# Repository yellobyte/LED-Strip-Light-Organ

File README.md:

# 3-Channel LED-Strip Light Organ with Arduino Nano #

A light (or color) organ is an electronic device which converts an audio signal into rhythmic light effects. Invented in the 70's they are still popular in discotheques and party rooms though.
Now that **LED Strips** became fairly cheap they can replace normal light bulbs used in the earlier years and make the color organ look more modern.

The electronic circuit of a normal light organ separates the audio signal into several frequency bands and dimms the light bulbs or LEDs according to the average level of each band.

For a decent visual impression at least 3 bands (channels) are needed: low frequencies (bass), middle frequencies and high frequencies (treble). For best visual results each channel should control a light source of different color, e.g bass = red, middle = yellow and treble = green.

## Technical Infos ##

We have 3 channels and therefore control 3 LED Strips. Their specified working voltage must be 12V DC. The maximum length of the LED Strips the device can handle is mainly determined by the current consumption (amperes per meter length) of each LED Strip and the maximum current rating of the external 12V power supply used.

To give you a real world example: The external power supply I tested the device with was a MeanWell GS90A12 with a maximum current rating of 6.7A DC. Therefore I set the overcurrent limit to 2.2A per channel (the device itself doesn't need much). That limit allowed me to use LED Strips of 5m length with 60 LEDs (Type 3528 SMD in red, yellow or green) per meter. The overcurrent protection circuitry never got triggered.

The light organ has 3 working modes: [Normal](https://github.com/yellobyte/LED-Strip-Light-Organ/blob/main/Doc/NormalMode.mp4), [Rhythm](https://github.com/yellobyte/LED-Strip-Light-Organ/blob/main/Doc/RhythmMode.mp4) and [Cyclic](https://github.com/yellobyte/LED-Strip-Light-Organ/blob/main/Doc/Cyclic.mp4), which can be selected by pressing the **mode selection** button. 

An Arduino Nano 328P continuously samples all 3 filter outputs und transforms their voltage levels into digital PWM signals which feed the output stages with their IRF540N Power MOSFETs. Overtemperature & overcurrent protection (overload OL protection) has been integrated. 

The electrical circuit had to be devided into 2 separate [PCBs](https://github.com/yellobyte/LED-Strip-Light-Organ/blob/main/Doc/BoardTop.JPG), a **Filter-PCB** and a **Power-PCB** as I only call the basic version of the Eagle Design Tool my own and PCB size is limited to Eurocard size. But this proved to be very fortunate in the end for I redesigned the output stages a few times but didn't have to redo the analog stages. Please have a look at folder [**EagleFiles**](https://github.com/yellobyte/LED-Strip-Light-Organ/blob/main/EagleFiles) for schematic & PCB details.

The block diagram of the light organ is as follows:

### The Filter-PCB: ###

The MC33078 Op amps in the pre-amplifier and AGC stages proved perfect for the task. They might be substituted with cheaper Op amps, e.g. TL082, TLC277 or MC1458 but this comes with a loss of signal quality (distortion!). Especially the MC1458 wasn't able to pull the signal fully down to the lower rail and the TLC277 showed some crossover distortion.

The cheap LM358 Op amps used in the 3 filter stages generate crossover distortion as well but this is of no consequence in that particular application.

The AGC stage is simple but very effective and produces hardly any distortion even with high input signals applied. This stage is needed in order to normalize the signal level fed into the filter stages as the signal level from the many audio sources can vary by an order of magnitude (MP3/CD/Vinyl player, FM or internet radio, etc.).

Each of the 3 filter circuits uses an Op amp and some passive components (Rs/Cs). The resistors with strange values (6k16, 14k7, 16k9, 23k7, 71k5) belong to the E48 (2%) or E96 (1%) series. The filter circuits (2nd order) were calculated with the help of **FilterLab** from Microchip. It's available at no cost, easy to use and very intuitive. 

LED1 to LED6 have been added mainly for testing purposes. They come handy when you don't have any LED-Strips available but still want to do some tests on the device. They too are PWM controlled and show the exact same visual effects as the LED-Strips would.

### The Power-PCB: ###

The Arduino Nano 328P module is an ideal device for sampling the three filter outputs and generating PWM signals needed by the power stages. It only runs on 16MHz but this proved fast enough for the task.

The code running on the Arduino Nano is available in folder [Software](https://github.com/yellobyte/LED-Strip-Light-Organ/blob/main/Software). It was generated with VSCode/PlatformIO.

The Power MOSFETs IRF540N work as High-Side Switches (in "common drain" configuration) and need a gate voltage higher than the Nano can provide in this application, thats why 12V DC-DC converters (I/O isolated -> output side floating) had to be used. The reason is that the source voltage of the MOSFETs approaches the +12V supply voltage when switched on. To keep the MOSFETs turned on the IR2125 outputs must drive the MOSFETs gate voltage 10-12V higher than the supply voltage.

Shunt resistors (R6/R12/R18 - 0.15Ohm/2W/5%/Wire) sit between the MOSFETs and the output sockets in order to measure the output current and utilize the current sense input of the MOSFET drivers IR2125. When the IR2125 detects overcurrent it shuts down immediately until the next PWM impuls. The software in the Arduino Nano detects this condition and shuts down the affected channel even longer (5 sec) before releasing it again. No harm is done at all in case you have a permanent short on the output lines, provided you properly calibrated the trigger point of course!

The power stages by design could deliver 3-4 amperes per channel without problems. In practice the limiting factor probably will be the external 12V DC power supply. The driver MOSFETs IRF540N (Idmax > 20A) operate way from their absolute maximum ratings and only get handwarm in the enclosure (Model EXN-23361-SV from Bud Industries).

A temperature sensor LM35DZ connected to an Arduino Nano analog input pin is used to measure the temperature inside the enclosure. Temperatures over 50° celsius will shut down all channels and only temperatures below 40° celsius will release them. However, during my hour long tests the temperature overload never got triggered for the temperature inside the enclosure always hovered around 35-38° celsius.

JP1/JP2/JP3 are only needed for testing purposes, in normal working mode pins 1 & 2 should be shorted in order to allow the overload signal from the IR2125 ICs reach the Arduino Nano. R2/SV3 are only used for testing purposes as well.

Push button S1 is used for selecting the working mode.

The three TVS Diodes P6KE20A (D5/D9/D13) in parallel with the output sockets have a very fast response time and protect the device from possibly harmful voltage transients that might travel in from connected LED Strips. The latter act like big antennas when a few meters long!

D1 provides a very stable reference voltage needed by the A/D converters in the Arduino Nano.

### The two [boards](https://github.com/yellobyte/LED-Strip-Light-Organ/blob/main/Doc/BoardTop.JPG) are connected as follows: ###

```c
 Filter-PCB ---  Power-PCB
      LSP7  ---  LSP9  (analog audio)
      LSP8  ---  LSP2  (+12V=)
      A-IN  ---  A-OUT (PWM channel A)
      B-IN  ---  B-OUT (PWM channel B)
      C-IN  ---  C-OUT (PWM channel C)
      A-OUT ---  A-IN  (filter output channel A)
      B-OUT ---  B-IN  (filter output channel B)
      C-OUT ---  C-IN  (filter output channel C)  
      GNDs  ---  GNDs   
```        

## How to calibrate the circuit ##

### Filter-PCB: ###
The pre-amplifier stage, the automatic gain control (AGC) stage and all three filter circuits have to be calibrated in order to produce optimal results. The procedure itself is fairly easy. Only obstacle is you need a function generator and ideally an oscilloscope. A cheap multimeter will do if you can´t get hold of such equipment but might spoil optimal performance of the device.

Necessary steps in correct order:

1) Adjust the trimpot R8 so that pins 1 & 2 of R8 are shorted (AGC is inactive that way). Apply a signal of 1kHz/0.5Vpp to X5 **or** X6 on the power board (one of the two Cinch/RCA sockets). It gets forwarded to LSP7 on the filter board (inverting input of pre-amplifier Op amp IC1A). 

2) Choose a value of R12 so that the signal level at LSP2 (output of Op amp IC1B) is close to 2.70Vpp. In my case I ended up with a R12 of 470k.

3) Increase the amplitude of the input signal to 2.0Vpp. Now adjust the trimpot R8 so that the signal level at LSP2 is close to 3.2Vpp.

At this point the pre-amplifier & AGC stages are properly calibrated. The filter stages follow:

4) Change the input signal to 50Hz/0.7Vpp and adjust R17 so that you get 3.6Vpp at LSP4.

5) Change the input signal to 1.3kHz/0.7Vpp and adjust R22 so that you get 3.6Vpp at LSP5.

6) Change the input signal to 6kHz/0.7Vpp and adjust R30 so that you get 3.6Vpp at LSP6.

That's it. The analog circuit on the **Filter-PCB** is now fully calibrated.

### Power-PCB: ###
Only the current limits of each channel (A/B/C) need to be calibrated. That's a bit tricky as you need a current running through the MOSFETs that has exactly the value you want the IR2125 to trigger. I used a cheap electronic load from Aliexpress (XY-FZ35) to accomplish that. 

Before you start make sure the Arduino Nano is REMOVED from the Power-PCB, your external power supply is NOT attached to the 12V power socket and there are NO jumpers on JP1/JP2/JP3 !

The following steps have to be done for each channel A/B/C, starting with channel A:

7) Adjust the trimpot R7 (R13/R19) so that U1 (U2/U3) pins 5 & 6 (CS & VS of IR2125) are shorted
8) Attach a voltmeter to LSP12 (LSP22/LSP32) and Ground
9) Attach the electronic load to the channel output socket (the socket for the LED-strip) and set the current limit to the desired trigger value 
10) Connect A-OUT (B/C-OUT) (IR2125 pin 2) with LSP2 (+12V=). That will switch the MOSFET on at the next step.
11) Now connect the external 12V power supply, the electronic load should see the programmed current flow
12) Slowly turn the screw on trimpot R7 (R13/R19) until the voltage on LSP12 (LSP22/LSP32) jumps from 0 to 4.7V. Stop turning immediately!
13) Remove the external 12V power supply and the electronic load 
14) Put the jumper back on pins 1 & 2 of JP1 (JP2/JP3) and remove the connection between LSP2 and A-OUT (B/C-OUT)
15) proceed with the next channel

Having all channels calibrated you can put the Arduino Nano back onto the board.
Those settings properly done for all channels, even a permanent short on the output sockets won't destroy your output stages.

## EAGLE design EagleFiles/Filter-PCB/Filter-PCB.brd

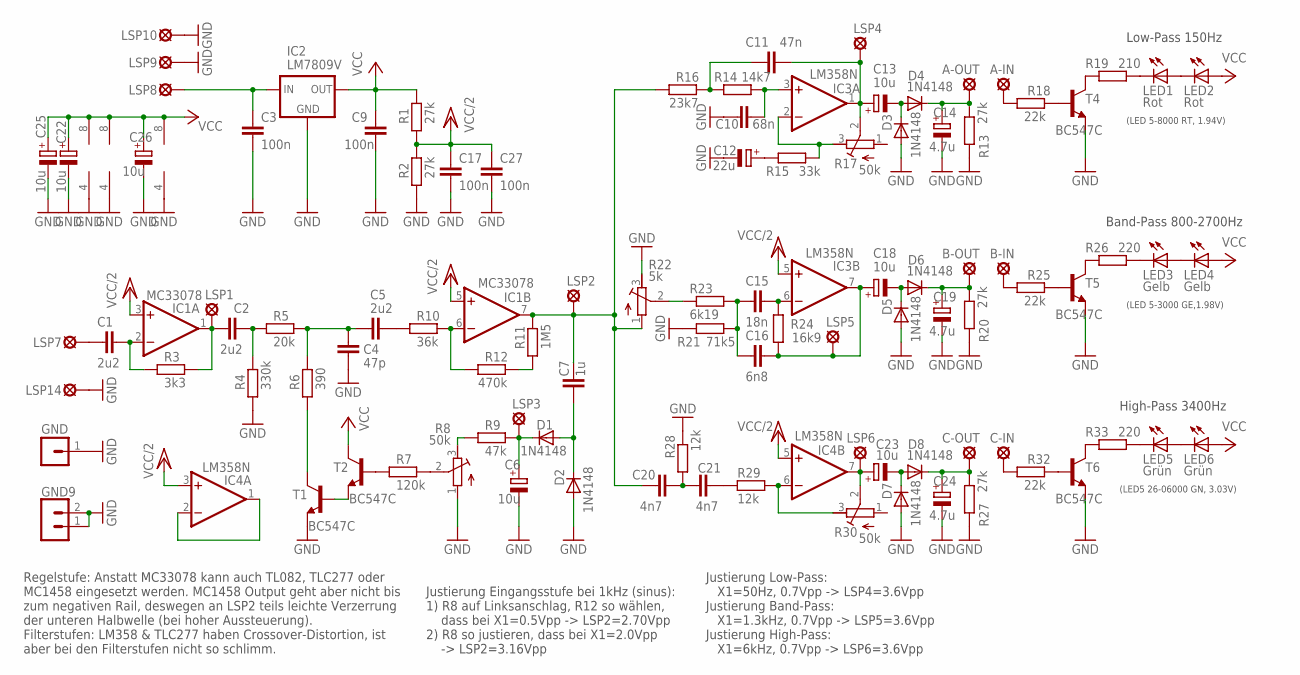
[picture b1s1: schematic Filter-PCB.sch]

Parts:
A-IN: LSP13
A-OUT: LSP13
B-IN: LSP13
B-OUT: LSP13
C1, C2, C5: 2u2; C1206
C3, C17: 100n; C050-024X044
C4: 47p; C1206
C6, C13, C18, C22, C23, C25, C26: 10u; TT2D4
C7: 1u; C050-024X044
C9, C27: 100n; C1206
C10: 68n; C1206
C11: 47n; C1206
C12: 22u; TT2D4
C14, C19, C24: 4.7u; TT2D4
C15: 18n; C1206
C16: 6n8; C1206
C20, C21: 4n7; C050-024X044
C-IN: LSP13
C-OUT: LSP13
D1, D2, D3, D4, D5, D6, D7, D8: 1N4148; SOD80C
GND: MA01-1
GND9: MA02-1
IC1: MC33078; DIL08
IC2: LM7809V; 78XXS
IC3, IC4: LM358N; DIL08
LED1, LED2: Rot; LED5MM
LED3, LED4: Gelb; LED5MM
LED5, LED6: Grün; LED5MM
LSP1, LSP2, LSP3, LSP4, LSP5, LSP6: LSP11
LSP7, LSP8, LSP9, LSP10, LSP14: LSP13
R1, R2: 27k; M1206
R3: 3k3; M1206
R4: 330k; M1206
R5: 20k; M1206
R6: 390; M1206
R7: 120k; M1206
R8, R17, R30: 50k; RTRIM64P
R9: 47k; M1206
R10: 36k; M1206
R11: 1M5; M1206
R12: 470k; 0207/10
R13, R20, R27: 27k; 0207/10
R14: 14k7; 0207/10
R15: 33k; M1206
R16: 23k7; 0207/10
R18, R25, R32: 22k; M1206
R19: 210; 0207/10
R21: 71k5; 0207/10
R22: 5k; RTRIM64P
R23: 6k19; 0207/10
R24: 16k9; 0207/10
R26, R33: 220; 0207/10
R28, R29: 12k; 0207/10
T1, T2, T4, T5, T6: BC547C; TO92

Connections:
GND: C3.2, C4.2, C6.-, C9.1, C10.1, C12.-, C14.-, C17.2, C19.-, C22.-, C24.-, C25.-, C26.-, C27.2, D2.A, D3.A, D5.A, D7.A, GND.1, GND9.1, GND9.2, IC1.4 (V-), IC2.GND, IC3.4 (V-), IC4.4 (V-), LSP9.MP, LSP10.MP, LSP14.MP, R2.1, R4.1, R8.1 (A), R13.1, R20.1, R21.1, R22.3 (E), R27.1, R28.2, T1.1 (E), T4.1 (E), T5.1 (E), T6.1 (E)
unnamed: R18.2, T4.2 (B)
unnamed: R25.2, T5.2 (B)
unnamed: R32.2, T6.2 (B)
unnamed: C1.2, IC1.2 (-IN), R3.1
unnamed: C2.2, R4.2, R5.1
unnamed: R6.1, T1.3 (C)
unnamed: C2.1, IC1.1 (OUT), LSP1.MP, R3.2
unnamed: C4.1, C5.1, R5.2, R6.2
unnamed: R7.1, T2.2 (B)
unnamed: R7.2, R8.2 (S)
unnamed: T1.2 (B), T2.1 (E)
unnamed: R8.3 (E), R9.1
unnamed: IC1.6 (-IN), R10.2, R12.1
unnamed: C7.1, C20.1, IC1.7 (OUT), LSP2.MP, R11.2, R16.1, R22.1 (A)
unnamed: C6.+, D1.C, LSP3.MP, R9.2
unnamed: C7.2, D1.A, D2.C
unnamed: C3.1, IC2.IN, LSP8.MP
unnamed: C11.1, R14.1, R16.2
unnamed: C5.2, R10.1
unnamed: R11.1, R12.2
unnamed: C10.2, IC3.3 (+IN), R14.2
unnamed: IC3.2 (-IN), R15.2, R17.3 (E)
unnamed: C11.2, C13.+, IC3.1 (OUT), LSP4.MP, R17.2 (S)
unnamed: C12.+, R15.1
unnamed: R22.2 (S), R23.1
unnamed: C13.-, D3.C, D4.A
unnamed: A-OUT.MP, C14.+, D4.C, R13.2
unnamed: C1.1, LSP7.MP
unnamed: R19.1, T4.3 (C)
unnamed: LED1.K (C), R19.2
unnamed: C24.+, C-OUT.MP, D8.C, R27.2
unnamed: C15.1, C16.1, R21.2, R23.2
unnamed: C15.2, IC3.6 (-IN), R24.2
unnamed: C21.2, R29.1
unnamed: C16.2, C18.+, IC3.7 (OUT), LSP5.MP, R24.1
unnamed: C20.2, C21.1, R28.1
unnamed: C18.-, D5.C, D6.A
unnamed: B-OUT.MP, C19.+, D6.C, R20.2
unnamed: A-IN.MP, R18.1
unnamed: R26.1, T5.3 (C)
unnamed: LED3.K (C), R26.2
unnamed: B-IN.MP, R25.1
unnamed: C23.+, IC4.7 (OUT), LSP6.MP, R30.2 (S)
unnamed: C-IN.MP, R32.1
unnamed: IC4.6 (-IN), R29.2, R30.3 (E)
unnamed: C23.-, D7.C, D8.A
unnamed: LED5.A, LED6.K (C)
unnamed: LED3.A, LED4.K (C)
unnamed: R33.1, T6.3 (C)
unnamed: LED5.K (C), R33.2
unnamed: LED1.A, LED2.K (C)
unnamed: IC4.1 (OUT), IC4.2 (-IN)
VCC: C9.2, C22.+, C25.+, C26.+, IC1.8 (V+), IC2.OUT, IC3.8 (V+), IC4.8 (V+), LED2.A, LED4.A, LED6.A, R1.2, T2.3 (C)
VCC/2: C17.1, C27.1, IC1.3 (+IN), IC1.5 (+IN), IC3.5 (+IN), IC4.3 (+IN), IC4.5 (+IN), R1.1, R2.2

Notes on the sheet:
Low-Pass 150Hz
Band-Pass 800-2700Hz
High-Pass 3400Hz
Justierung Eingangsstufe bei 1kHz (sinus): 1) R8 auf Linksanschlag, R12 so wählen, dass bei X1=0.5Vpp -> LSP2=2.70Vpp 2) R8 so justieren, dass bei X1=2.0Vpp -> LSP2=3.16Vpp
Justierung Low-Pass: X1=50Hz, 0.7Vpp -> LSP4=3.6Vpp Justierung Band-Pass: X1=1.3kHz, 0.7Vpp -> LSP5=3.6Vpp Justierung High-Pass: X1=6kHz, 0.7Vpp -> LSP6=3.6Vpp
Regelstufe: Anstatt MC33078 kann auch TL082, TLC277 oder MC1458 eingesetzt werden. MC1458 Output geht aber nicht bis zum negativen Rail, deswegen an LSP2 teils leichte Verzerrung der unteren Halbwelle (bei hoher Aussteuerung). Filterstufen: LM358 & TLC277 haben Crossover-Distortion, ist aber bei de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
(LED 5-8000 RT, 1.94V)
(LED 5-3000 GE,1.98V)
(LED5 26-06000 GN, 3.03V)

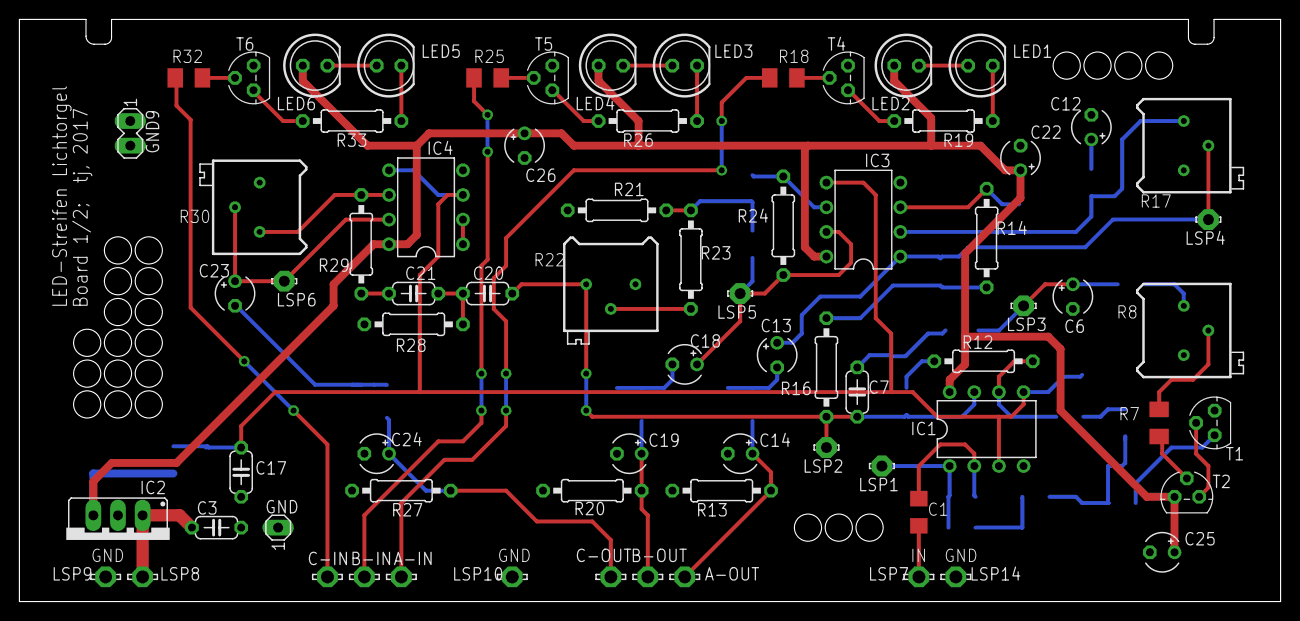
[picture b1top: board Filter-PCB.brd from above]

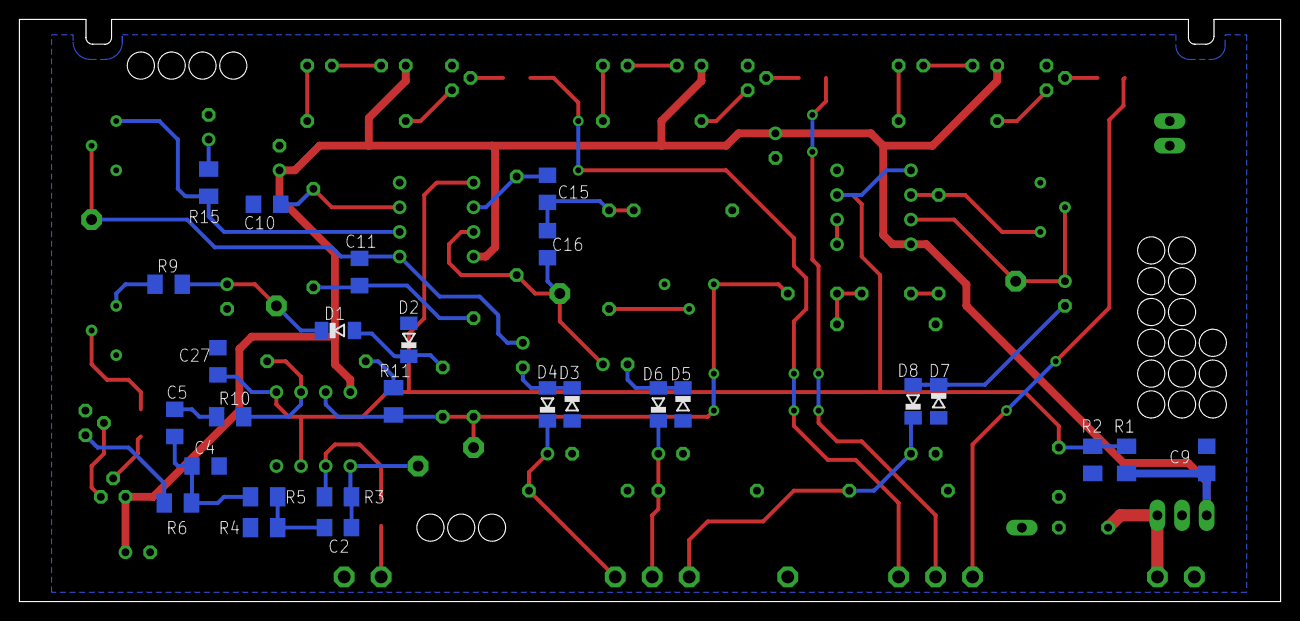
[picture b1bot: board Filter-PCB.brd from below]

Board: 2 copper layers, 130.0 x 60.0 mm, 100 parts (27 on the bottom side), 55 nets.

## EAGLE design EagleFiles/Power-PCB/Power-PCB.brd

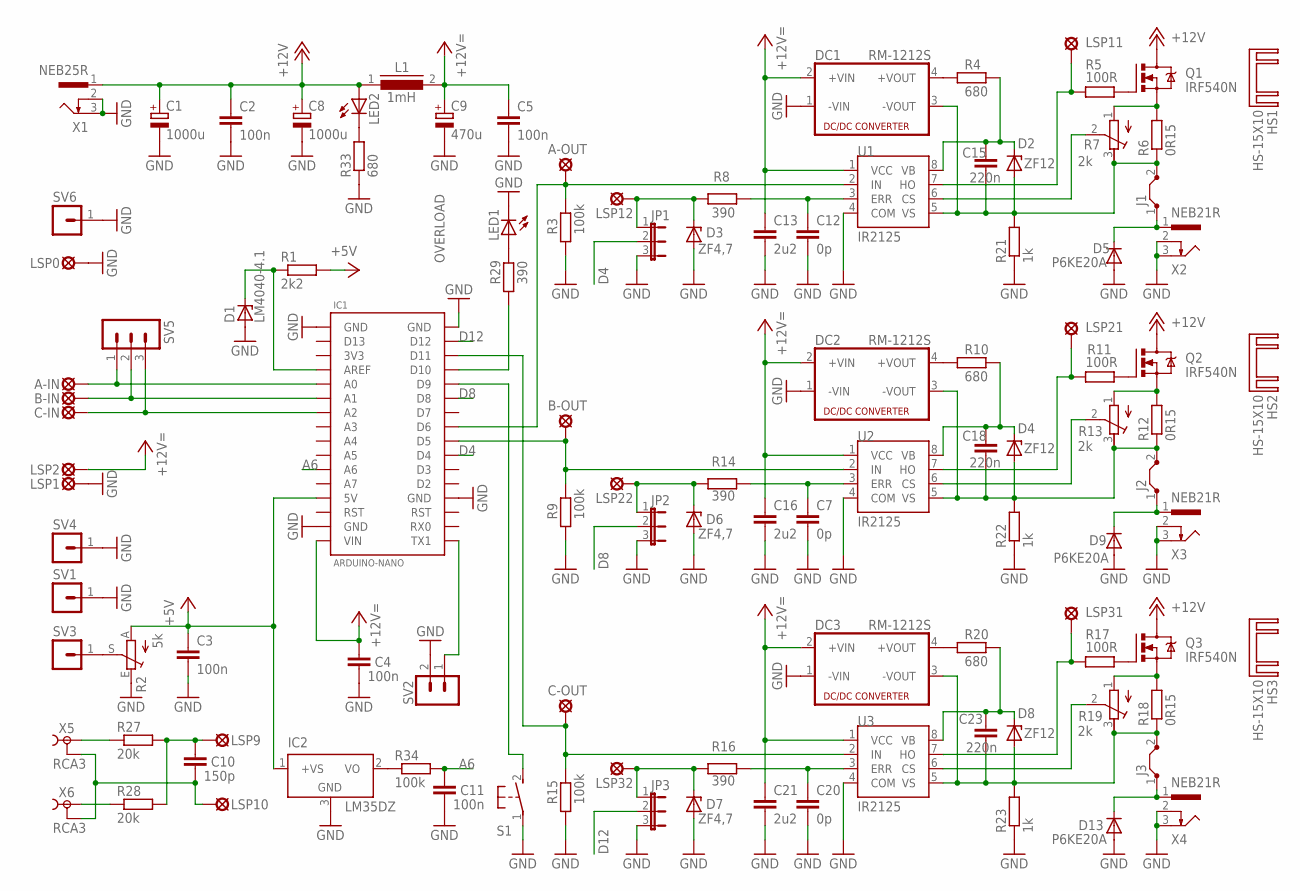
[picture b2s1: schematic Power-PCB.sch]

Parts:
A-IN: LSP13
A-OUT: LSP13
B-IN: LSP13
B-OUT: LSP13
C1, C8: 1000u; E5-13
C2, C3, C4, C5, C11: 100n; C050-024X044
C7, C12, C20: 0p; C025-024X044
C9: 470u; E5-10,5
C10: 150p; C025-024X044
C13, C16, C21: 2u2; C1206
C15, C18, C23: 220n; C050-024X044
C-IN: LSP13
C-OUT: LSP13
D1: LM4040-4.1; TO-92
D2, D4, D8: ZF12; DO34Z7
D3, D6, D7: ZF4,7; DO34Z7
D5, D9, D13: P6KE20A; C1702-05
DC1, DC2, DC3: RM-1212S; NME
HS1, HS2, HS3: HS-15X10; HEATSINK-TO220-15X10X21
IC1: ARDUINO-NANO
IC2: LM35DZ; TO92
J1, J2, J3: JUMPER-BRIGDE12MM; 12-THICK-WIRE
JP1, JP2, JP3: JP2E; JP2
L1: 1mH; L-09HCP
LED1: LED5MM
LED2: LED3MM
LSP0, LSP1, LSP2, LSP9, LSP10: LSP13
LSP11, LSP12, LSP21, LSP22, LSP31, LSP32: LSP11
Q1, Q2, Q3: IRF540N; TO220BV
R1: 2k2; M1206
R2: 5k; PT-10
R3, R9, R15: 100k; 0207/10
R4, R10, R20: 680; 0207/10
R5, R11, R17: 100R; M1206
R6, R12, R18: 0R15; 0617V
R7, R13, R19: 2k; RTRIM64W
R8, R14, R16: 390; M1206
R21, R22, R23: 1k; 0207/2V
R27, R28: 20k; M1206
R29: 390; 0207/10
R33: 680; M1206
R34: 100k; M1206
S1: 31-XX; B3F-31XX
SV1, SV3, SV4, SV6: MA01-1
SV2: MA02-1
SV5: MA03-1
U1, U2, U3: IR2125; DIL08
X1: NEB25R; NEB21R
X2, X3, X4: NEB21R
X5, X6: RCA3

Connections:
3V3: IC1.3V3
+5V: C3.1, IC1.+5V (5V), IC2.1 (+VS), R1.2, R2.A
+12V: C1.+, C2.1, C8.+, L1.1, LED2.A, Q1.D, Q2.D, Q3.D, X1.1
+12V=: C4.1, C5.1, C9.+, C13.1, C16.1, C21.1, DC1.2 (+VIN), DC2.2 (+VIN), DC3.2 (+VIN), IC1.VIN, L1.2, LSP2.MP, U1.1 (VCC), U2.1 (VCC), U3.1 (VCC)
A6: C11.1, IC1.A6, R34.2
AREF: D1.2 (C), IC1.AREF, R1.1
D4: IC1.D4, JP1.2
D5: B-OUT.MP, IC1.D5, R9.2, U2.2 (IN)
D6: A-OUT.MP, IC1.D6, R3.2, U1.2 (IN)
D8: IC1.D8, JP2.2
D11: C-OUT.MP, IC1.D11, R15.2, U3.2 (IN)
D12: IC1.D12, JP3.2
GND: C1.-, C2.2, C3.2, C4.2, C5.2, C7.2, C8.-, C9.-, C11.2, C12.2, C13.2, C16.2, C20.2, C21.2, D1.3 (A), D3.A, D5.A, D6.A, D7.A, D9.A, D13.A, DC1.1 (-VIN), DC2.1 (-VIN), DC3.1 (-VIN), IC1.GND, IC1.GND1 (GND), IC1.GND2 (GND), IC1.GND3 (GND), IC2.3 (GND), JP1.3, JP2.3, JP3.3, LED1.K (C), LSP0.MP, LSP1.MP, R2.E, R3.1, R9.1, R15.1, R21.1, R22.1, R23.1, R33.1, S1.1, SV1.1, SV2.2, SV4.1, SV6.1, U1.4 (COM), U2.4 (COM), U3.4 (COM), X1.2, X1.3, X2.2, X2.3, X3.2, X3.3, X4.2, X4.3
unnamed: LED1.A, R29.2
unnamed: A-IN.MP, IC1.A0, SV5.1
unnamed: B-IN.MP, IC1.A1, SV5.2
unnamed: C-IN.MP, IC1.A2, SV5.3
unnamed: C12.1, R8.1, U1.3 (ERR)
unnamed: IC1.TX1, SV2.1
unnamed: IC2.2 (VO), R34.1
unnamed: DC1.4 (+VOUT), R4.1
unnamed: D5.C, J1.1, X2.1
unnamed: C7.1, R14.1, U2.3 (ERR)
unnamed: DC2.4 (+VOUT), R10.1
unnamed: R7.2 (S), U1.6 (CS)
unnamed: C20.1, R16.1, U3.3 (ERR)
unnamed: LED2.K (C), R33.2
unnamed: DC3.4 (+VOUT), R20.1
unnamed: Q1.G, R5.2
unnamed: Q1.S, R6.2, R7.1 (A)
unnamed: Q2.S, R12.2, R13.1 (A)
unnamed: Q3.S, R18.2, R19.1 (A)
unnamed: LSP11.MP, R5.1, U1.7 (HO)
unnamed: D6.C, JP2.1, LSP22.MP, R14.2
unnamed: Q2.G, R11.2
unnamed: LSP21.MP, R11.1, U2.7 (HO)
unnamed: R13.2 (S), U2.6 (CS)
unnamed: D9.C, J2.1, X3.1
unnamed: R2.S, SV3.1
unnamed: Q3.G, R17.2
unnamed: LSP31.MP, R17.1, U3.7 (HO)
unnamed: R19.2 (S), U3.6 (CS)
unnamed: D13.C, J3.1, X4.1
unnamed: D3.C, JP1.1, LSP12.MP, R8.2
unnamed: D7.C, JP3.1, LSP32.MP, R16.2
unnamed: R27.1, X5.1
unnamed: R28.1, X6.1
unnamed: C10.2, LSP10.MP, X5.2, X5.2@1 (2), X5.2@2 (2), X6.2, X6.2@1 (2), X6.2@2 (2)
unnamed: C10.1, LSP9.MP, R27.2, R28.2
unnamed: IC1.D9, S1.2 (S)
OVERLOAD: IC1.D10, R29.1
VBU1: C15.1, D2.C, R4.2, U1.8 (VB)
VBU2: C18.1, D4.C, R10.2, U2.8 (VB)
VBU3: C23.1, D8.C, R20.2, U3.8 (VB)
VSU1: C15.2, D2.A, DC1.3 (-VOUT), J1.2, R6.1, R7.3 (E), R21.2, U1.5 (VS)
VSU2: C18.2, D4.A, DC2.3 (-VOUT), J2.2, R12.1, R13.3 (E), R22.2, U2.5 (VS)
VSU3: C23.2, D8.A, DC3.3 (-VOUT), J3.2, R18.1, R19.3 (E), R23.2, U3.5 (VS)

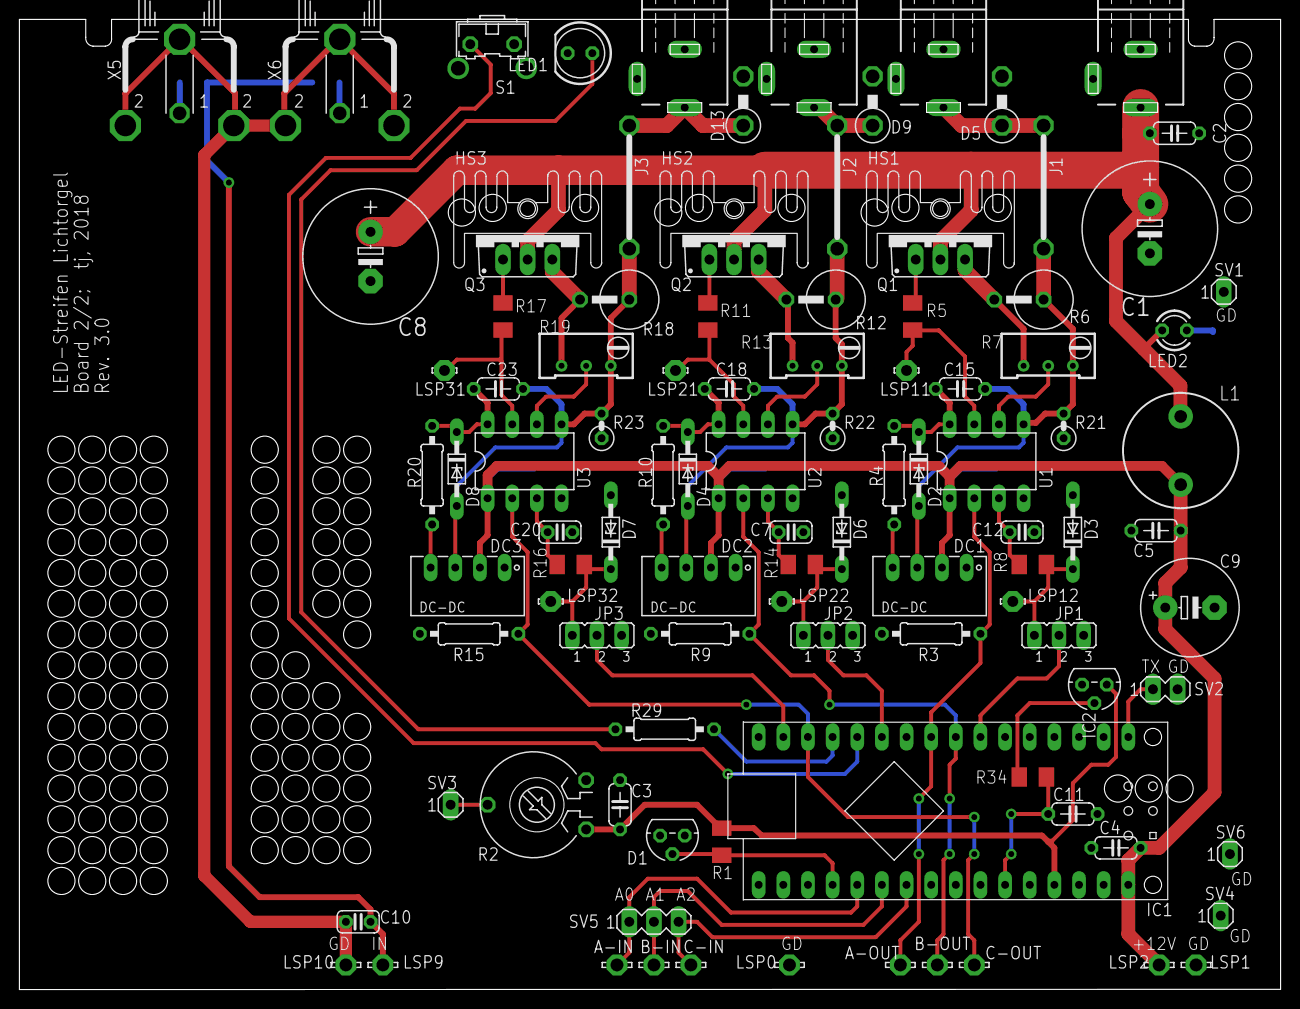
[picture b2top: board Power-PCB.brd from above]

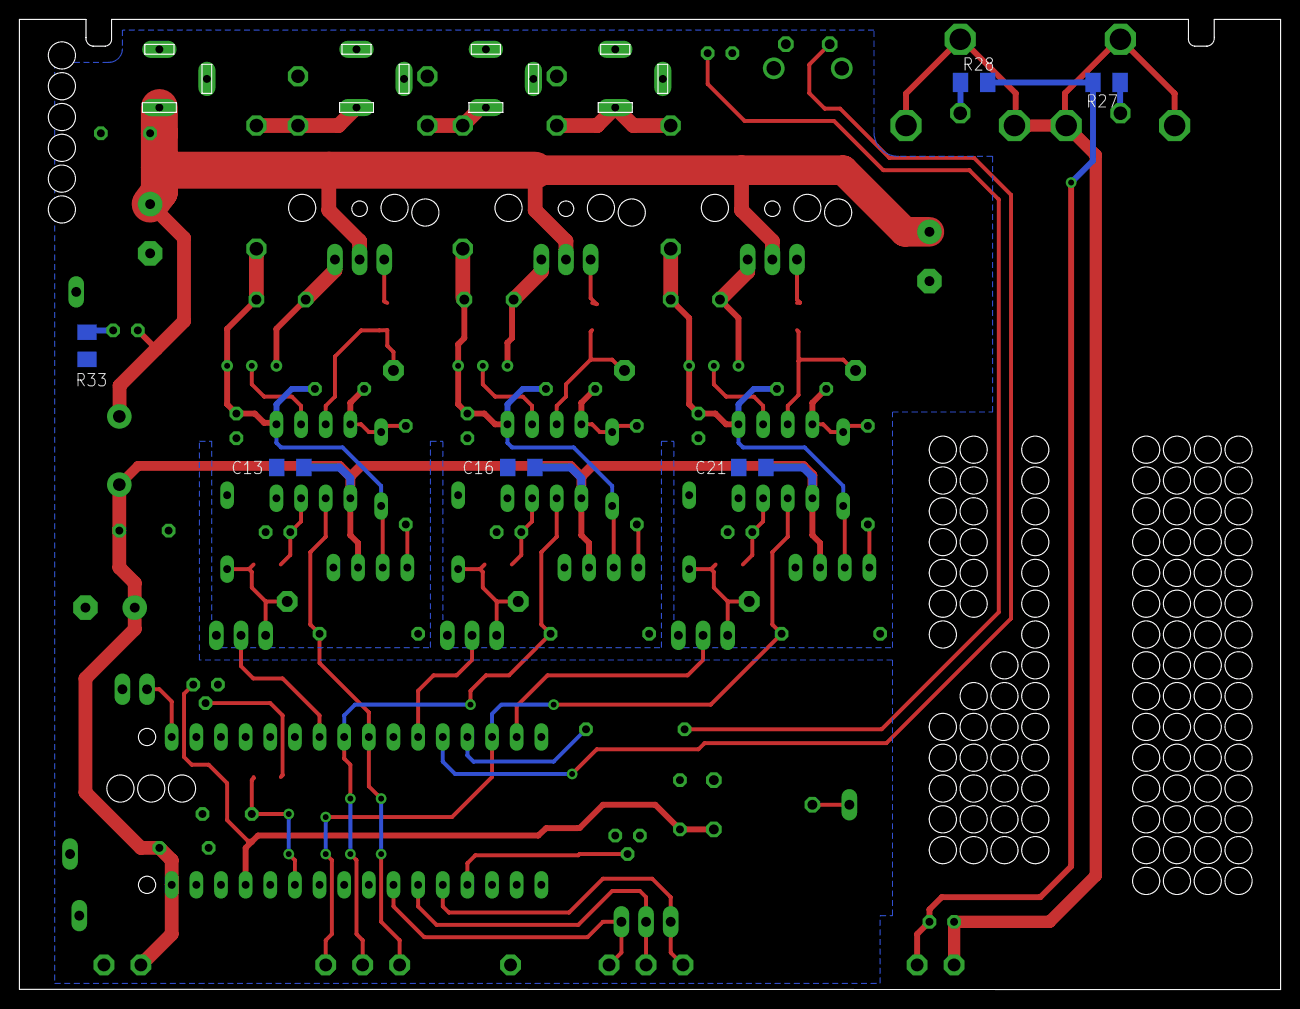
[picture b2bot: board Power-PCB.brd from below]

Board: 2 copper layers, 130.0 x 100.0 mm, 109 parts (6 on the bottom side), 56 nets.

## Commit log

2021-04-23 First upload
2021-04-23 resolution changed
2021-04-24 pics added
2021-04-24 Readme changed
2021-04-24 Readme.md updated
2021-04-25 Readme.md changed
2021-04-26 formatting fixed
2021-04-26 Block diagram improved
2021-04-26 text formatting fixed
2021-04-30 Initial upload
2021-05-04 File name fixed
2022-04-21 SPICE simu of AGC stage added
